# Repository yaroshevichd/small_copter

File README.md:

# small (indoor) quadrocopter from scratch

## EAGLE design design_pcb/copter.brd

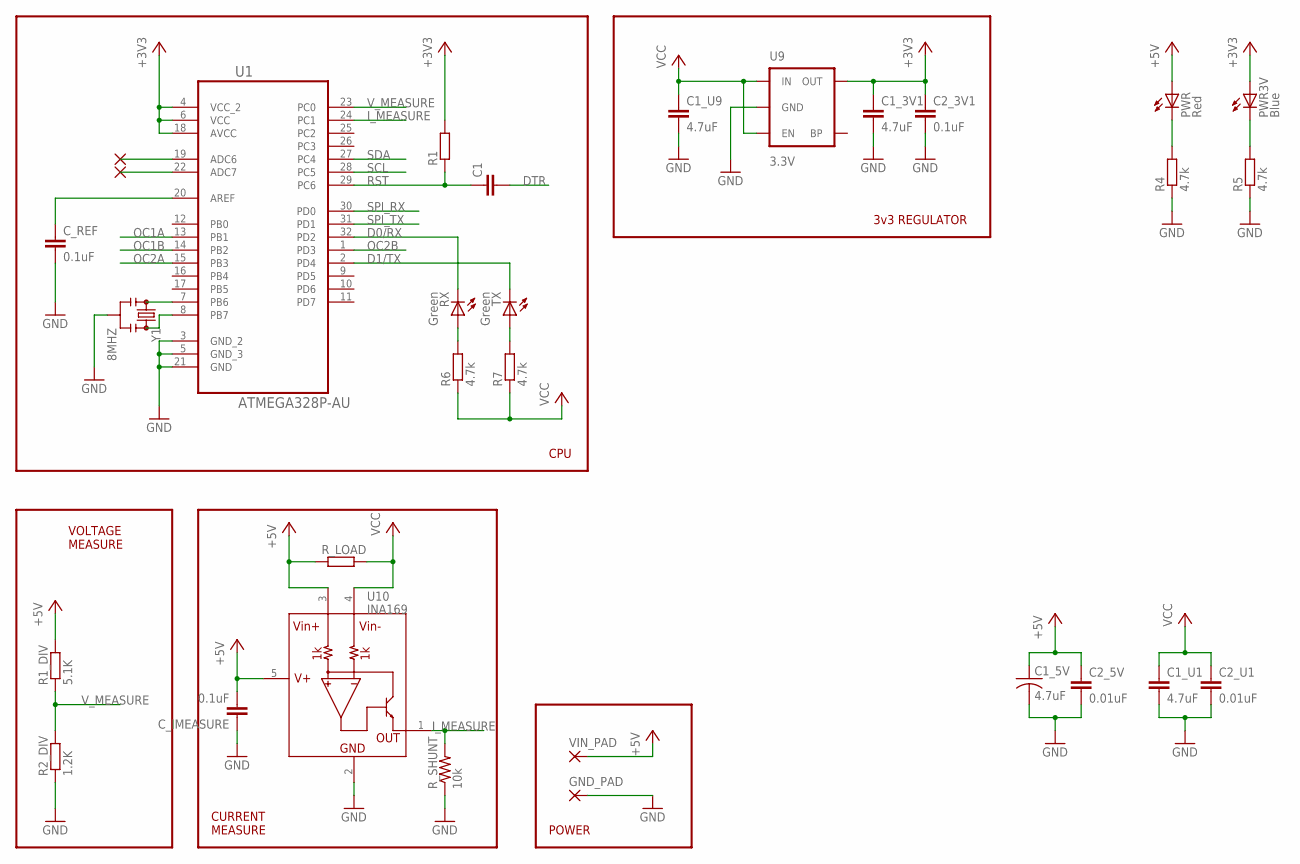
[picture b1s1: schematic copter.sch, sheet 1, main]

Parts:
C1: C-EUC0402; C0402
C1_3V1, C1_U9: 4.7uF; 0402-CAP
C1_5V: 4.7uF; C1210K
C1_U1: 4.7uF; C1206
C2_3V1: 0.1uF; 0402-CAP
C2_5V, C2_U1: 0.01uF; C0402
C_IMEASURE: 0.1uF; 0603-CAP
C_REF: 0.1uF; C0402
GND_PAD: 1,6/0,8
PWR: Red; LED-0603
PWR3V: Blue; LED-0603
R1: R-EU_R0402; R0402
R1_DIV: 5.1K; R0402
R2_DIV: 1.2K; R0402
R4, R5, R6, R7: 4.7k; R0402
RX: Green; LED-0603
R_LOAD: R-EU_0309/10; 0309/10
R_SHUNT: 10k; 0603-RES
TX: Green; LED-0603
U1: ATMEGA328P-AU; QFP80P900X900X120-32N
U9: 3.3V; SOT23-5
U10: INA169; SOT23-5
VIN_PAD: 1,6/0,8
Y1: 8MHZ; RESONATOR-SMD

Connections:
+3V3: C1_3V1.1, C2_3V1.1, PWR3V.A, R1.2, U1.4 (VCC_2), U1.6 (VCC), U1.18 (AVCC), U9.5 (OUT); also elsewhere on the board
+5V: C1_5V.1, C2_5V.1, C_IMEASURE.2, PWR.A, R1_DIV.2, R_LOAD.1, U10.3 (VIN+), U10.5 (V+), VIN_PAD.1; also elsewhere on the board
D0/RX: RX.C, U1.32 (PD2); also elsewhere on the board
D1/TX: TX.C, U1.2 (PD4); also elsewhere on the board
DTR: C1.2; also elsewhere on the board
GND: C1_3V1.2, C1_5V.2, C1_U1.2, C1_U9.2, C2_3V1.2, C2_5V.2, C2_U1.2, C_IMEASURE.1, C_REF.2, GND_PAD.1, R2_DIV.1, R4.1, R5.1, R_SHUNT.1, U1.3 (GND_2), U1.5 (GND_3), U1.21 (GND), U9.2 (GND), U10.2 (GND), Y1.2; also elsewhere on the board
I_MEASURE: R_SHUNT.2, U1.24 (PC1), U10.1 (OUT)
unnamed: R7.2, TX.A
unnamed: R6.2, RX.A
unnamed: PWR.C, R4.2
unnamed: PWR3V.C, R5.2
unnamed: C_REF.1, U1.20 (AREF)
unnamed: U1.7 (PB6), Y1.1
unnamed: U1.8 (PB7), Y1.3
OC1A: U1.13 (PB1); also elsewhere on the board
OC1B: U1.14 (PB2); also elsewhere on the board
OC2A: U1.15 (PB3); also elsewhere on the board
OC2B: U1.1 (PD3); also elsewhere on the board
RST: C1.1, R1.1, U1.29 (PC6)
SCL: U1.28 (PC5); also elsewhere on the board
SDA: U1.27 (PC4); also elsewhere on the board
SPI_RX: U1.30 (PD0); also elsewhere on the board
SPI_TX: U1.31 (PD1); also elsewhere on the board
VCC: C1_U1.1, C1_U9.1, C2_U1.1, R6.1, R7.1, R_LOAD.2, U9.1 (IN), U9.3 (EN), U10.4 (VIN-); also elsewhere on the board
V_MEASURE: R1_DIV.1, R2_DIV.2, U1.23 (PC0)

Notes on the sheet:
VOLTAGE MEASURE
CURRENT MEASURE
CPU
3v3 REGULATOR
POWER

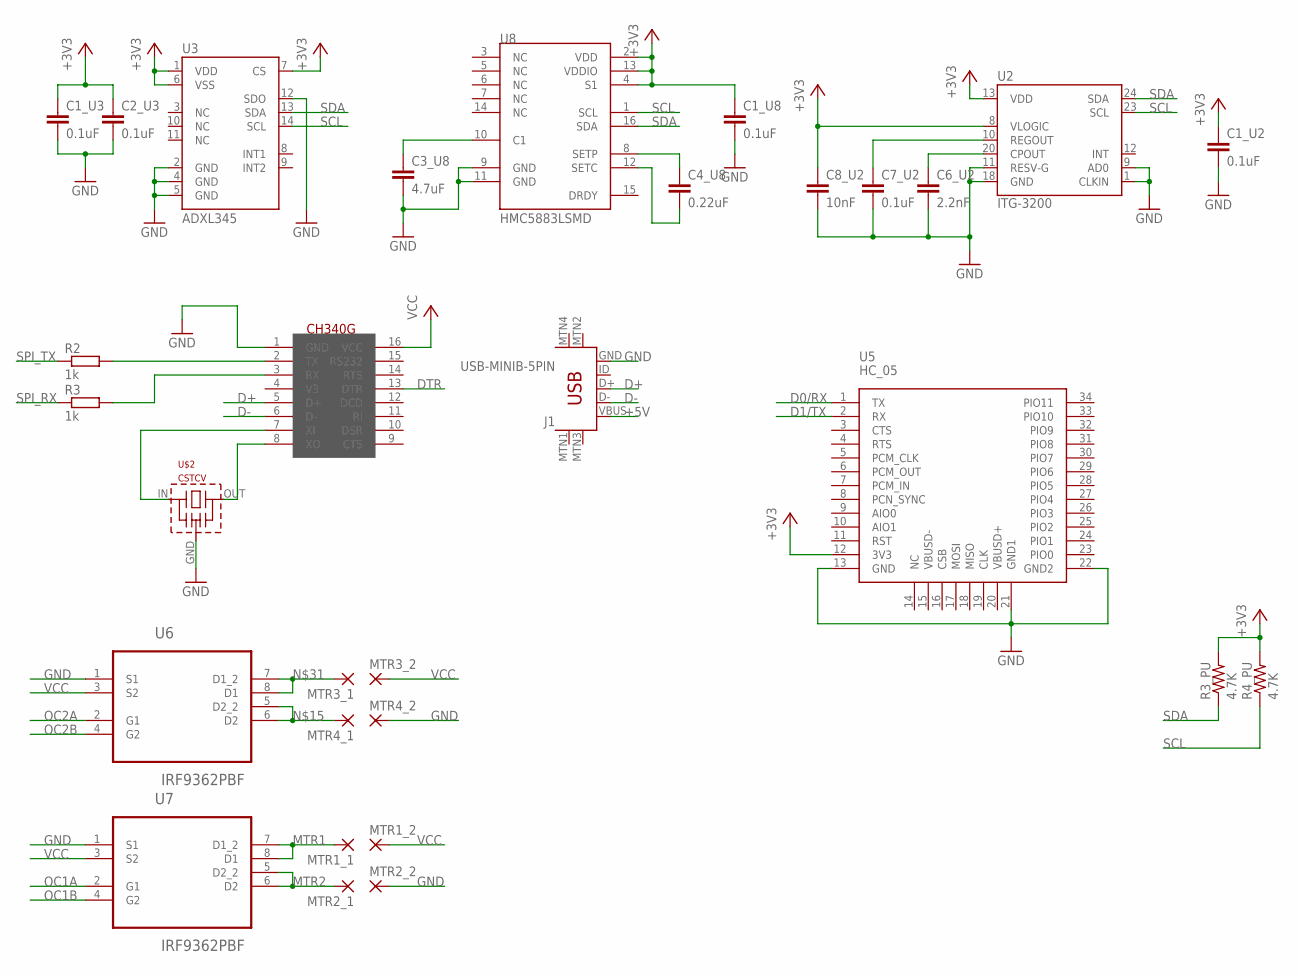
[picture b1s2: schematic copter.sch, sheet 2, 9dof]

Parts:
C1_U2, C1_U3, C1_U8, C2_U3, C7_U2: 0.1uF; 0402-CAP
C3_U8: 4.7uF; 0402-CAP
C4_U8: 0.22uF; 0402-CAP
C6_U2: 2.2nF; 0402-CAP
C8_U2: 10nF; 0402-CAP
J1: USB-MINIB-5PIN; USB-MINIB
MTR1_1, MTR1_2, MTR2_1, MTR2_2, MTR3_1, MTR3_2, MTR4_1, MTR4_2: 1,6/0,8
R2, R3: 1k; R0402
R3_PU, R4_PU: 4.7K; 0402-RES
U2: ITG-3200; QFN-24
U3: ADXL345; LGA14
U5: HC_05; BLUETOOTH_SMD
U6, U7: IRF9362PBF; SOIC127P600X175-8N
U8: HMC5883LSMD; 16LPCC
U$1: CH340G; SOIC16
U$2: CSTCV

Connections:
+3V3: C1_U2.1, C1_U3.1, C1_U8.1, C2_U3.1, C8_U2.1, R3_PU.2, R4_PU.2, U2.8 (VLOGIC), U2.13 (VDD), U3.1 (VDD), U3.6 (VSS), U3.7 (CS), U5.12 (3V3), U8.2 (VDD), U8.4 (S1), U8.13 (VDDIO); also elsewhere on the board
+5V: J1.VBUS; also elsewhere on the board
D0/RX: U5.1 (TX); also elsewhere on the board
D1/TX: U5.2 (RX); also elsewhere on the board
D+: J1.D+, U$1.5 (D+)
D-: J1.D-, U$1.6 (D-)
DTR: U$1.13 (DTR); also elsewhere on the board
GND: C1_U2.2, C1_U3.2, C1_U8.2, C2_U3.2, C3_U8.2, C6_U2.2, C7_U2.2, C8_U2.2, J1.GND, MTR2_2.1, MTR4_2.1, U2.1 (CLKIN), U2.9 (AD0), U2.11 (RESV-G), U2.18 (GND), U3.2 (GND), U3.4 (GND), U3.5 (GND), U3.12 (SDO), U5.13 (GND), U5.21 (GND1), U5.22 (GND2), U6.1 (S1), U7.1 (S1), U8.9 (GND), U8.11 (GND), U$1.1 (GND), U$2.GND; also elsewhere on the board
MTR1: MTR1_1.1, U7.7 (D1_2), U7.8 (D1)
MTR2: MTR2_1.1, U7.5 (D2_2), U7.6 (D2)
unnamed: R2.2, U$1.2 (TX)
unnamed: C6_U2.1, U2.20 (CPOUT)
unnamed: R3.2, U$1.3 (RX)
unnamed: C7_U2.1, U2.10 (REGOUT)
unnamed: U$1.8 (XO), U$2.OUT
unnamed: C3_U8.1, U8.10 (C1)
unnamed: C4_U8.1, U8.8 (SETP)
unnamed: C4_U8.2, U8.12 (SETC)
unnamed: MTR4_1.1, U6.5 (D2_2), U6.6 (D2)
unnamed: U$1.7 (XI), U$2.IN
unnamed: MTR3_1.1, U6.7 (D1_2), U6.8 (D1)
OC1A: U7.2 (G1); also elsewhere on the board
OC1B: U7.4 (G2); also elsewhere on the board
OC2A: U6.2 (G1); also elsewhere on the board
OC2B: U6.4 (G2); also elsewhere on the board
SCL: R4_PU.1, U2.23 (SCL), U3.14 (SCL), U8.1 (SCL); also elsewhere on the board
SDA: R3_PU.1, U2.24 (SDA), U3.13 (SDA), U8.16 (SDA); also elsewhere on the board
SPI_RX: R3.1; also elsewhere on the board
SPI_TX: R2.1; also elsewhere on the board
VCC: MTR1_2.1, MTR3_2.1, U6.3 (S2), U7.3 (S2), U$1.16 (VCC); also elsewhere on the board

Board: 2 copper layers, 59 parts (16 on the bottom side), 40 nets, no tracks yet.

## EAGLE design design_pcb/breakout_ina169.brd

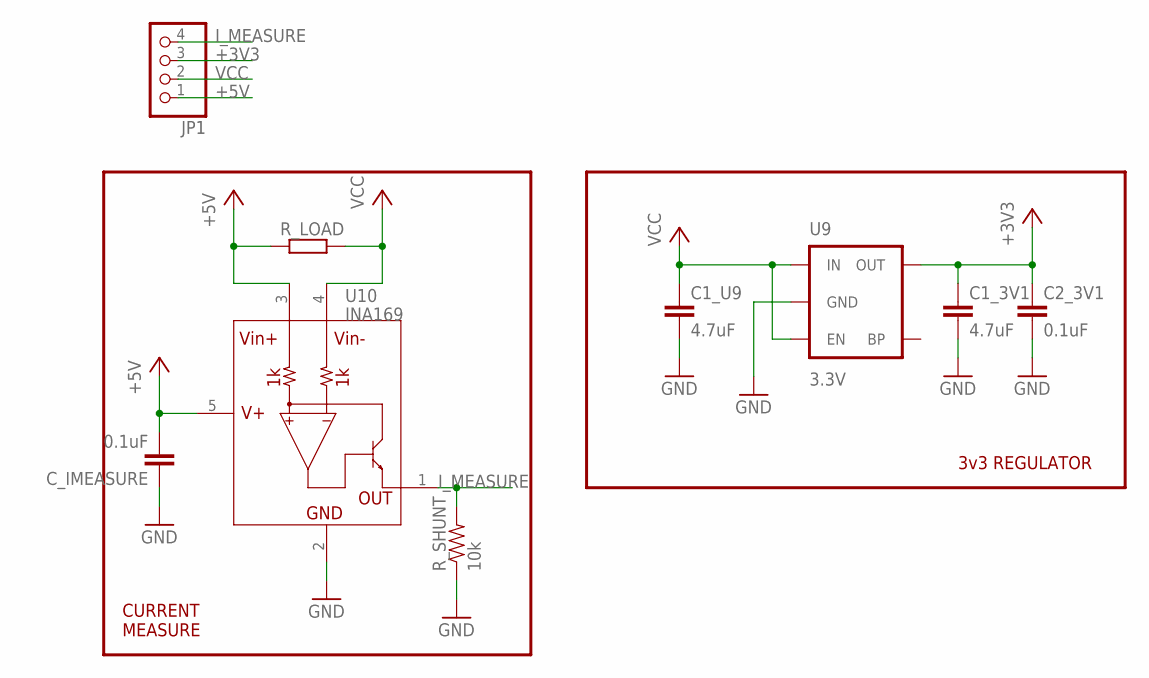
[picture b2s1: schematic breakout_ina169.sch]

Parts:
C1_3V1, C1_U9: 4.7uF; 0402-CAP
C2_3V1: 0.1uF; 0402-CAP
C_IMEASURE: 0.1uF; 0603-CAP
JP1: PINHD-1X4; 1X04
R_LOAD: R-EU_0309/10; 0309/10
R_SHUNT: 10k; 0603-RES
U9: 3.3V; SOT23-5
U10: INA169; SOT23-5

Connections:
+3V3: C1_3V1.1, C2_3V1.1, JP1.3, U9.5 (OUT)
+5V: C_IMEASURE.2, JP1.1, R_LOAD.1, U10.3 (VIN+), U10.5 (V+)
GND: C1_3V1.2, C1_U9.2, C2_3V1.2, C_IMEASURE.1, R_SHUNT.1, U9.2 (GND), U10.2 (GND)
I_MEASURE: JP1.4, R_SHUNT.2, U10.1 (OUT)
VCC: C1_U9.1, JP1.2, R_LOAD.2, U9.1 (IN), U9.3 (EN), U10.4 (VIN-)

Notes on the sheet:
CURRENT MEASURE
3v3 REGULATOR

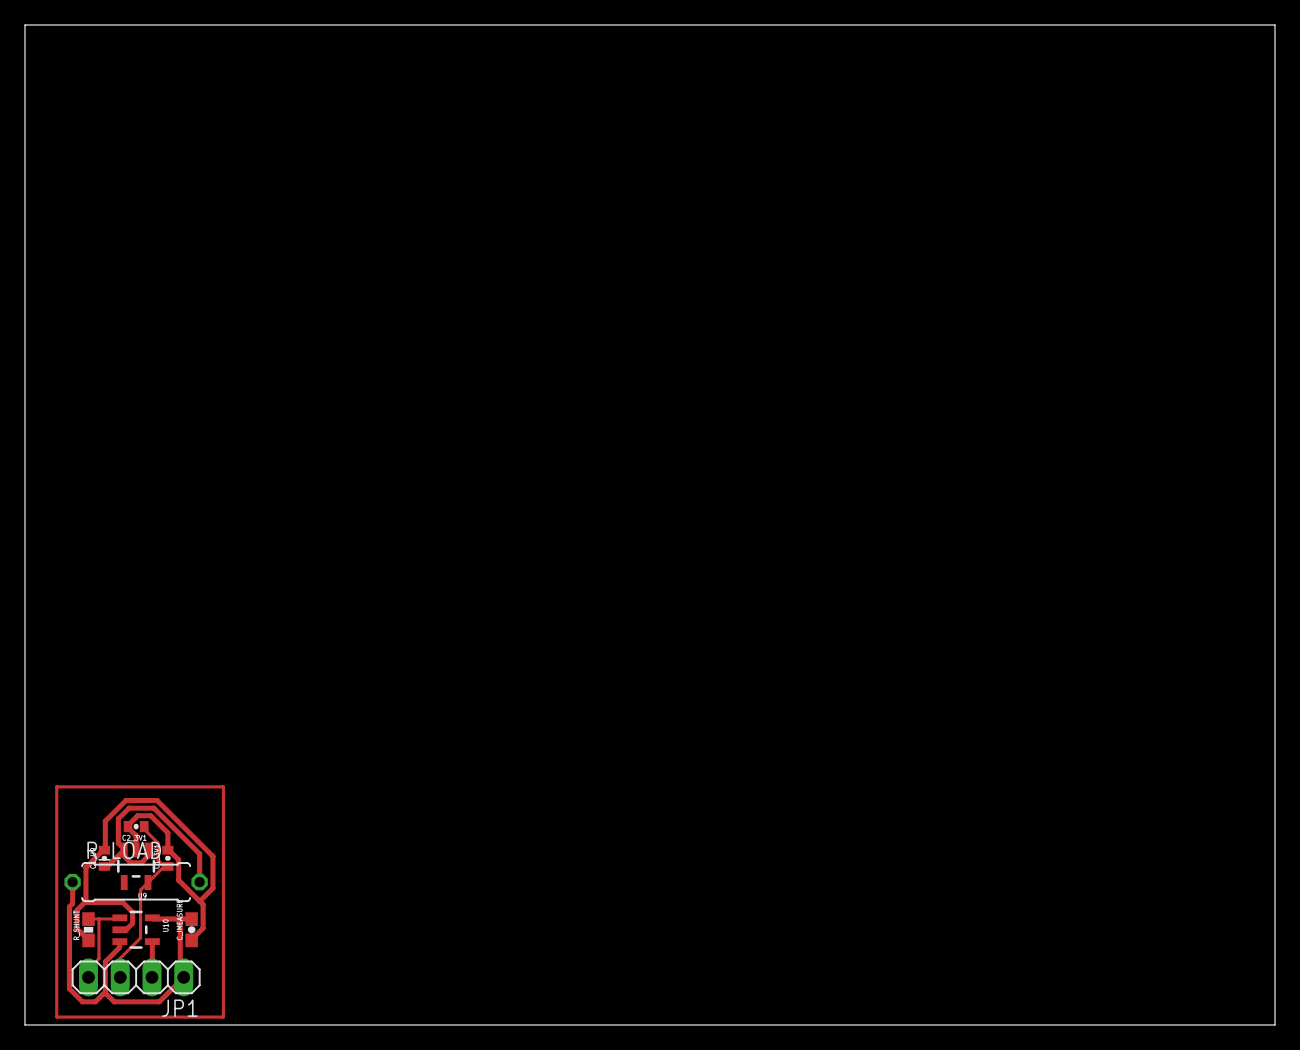
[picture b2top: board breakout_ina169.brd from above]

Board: 2 copper layers, 100.0 x 80.0 mm, 9 parts (0 on the bottom side), 5 nets.

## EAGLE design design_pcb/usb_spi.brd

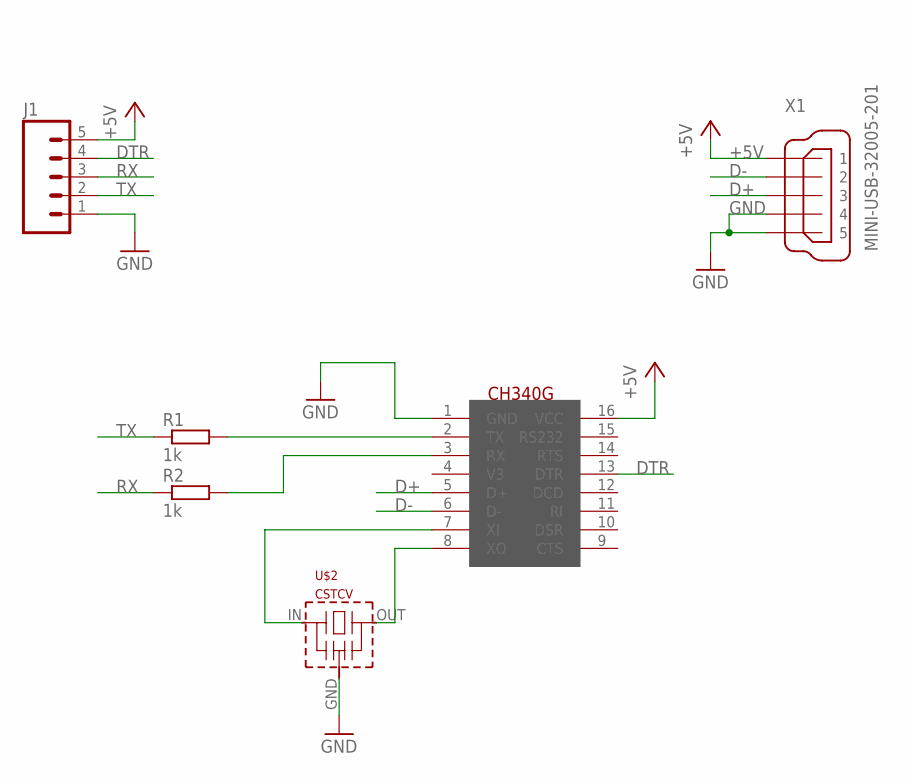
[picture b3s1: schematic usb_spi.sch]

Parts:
J1: M05PTH; 1X05
R1, R2: 1k; R0402
U$1: CH340G; SOIC16
U$2: CSTCV
X1: MINI-USB-32005-201; 32005-201

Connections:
+5V: J1.5, U$1.16 (VCC), X1.1
D+: U$1.5 (D+), X1.3
D-: U$1.6 (D-), X1.2
DTR: J1.4, U$1.13 (DTR)
GND: J1.1, U$1.1 (GND), U$2.GND, X1.4, X1.5
unnamed: R1.2, U$1.2 (TX)
unnamed: U$1.8 (XO), U$2.OUT
unnamed: R2.2, U$1.3 (RX)
unnamed: U$1.7 (XI), U$2.IN
RX: J1.3, R2.1
TX: J1.2, R1.1

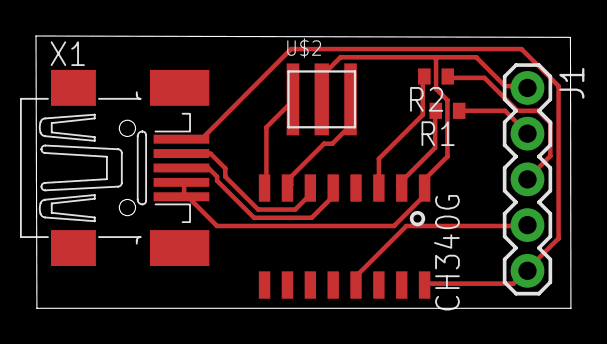
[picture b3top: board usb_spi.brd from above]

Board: 2 copper layers, 29.7 x 15.1 mm, 6 parts (0 on the bottom side), 11 nets.

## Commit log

2016-04-03 Add test programs
2016-04-05 Print x,y coordinates for tests purpose
2016-04-10 Update schematic and PCB
2016-05-04 move some components
2016-05-09 replace *4 resistor with 4 separate resistors
2016-05-31 add breakout boards

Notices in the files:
parts and their libraries:
SparkFun-Passives: Licensing: CC v3.0 Share-Alike You are welcome to use this library for commercial purposes.
SparkFun-FreqCtrl: Licensing: Creative Commons ShareAlike 4.0 International - https://creativecommons.org/licenses/by-sa/4.0
